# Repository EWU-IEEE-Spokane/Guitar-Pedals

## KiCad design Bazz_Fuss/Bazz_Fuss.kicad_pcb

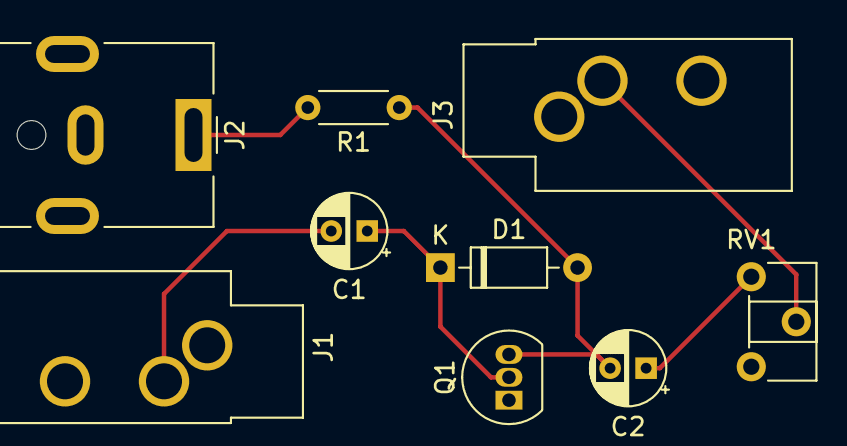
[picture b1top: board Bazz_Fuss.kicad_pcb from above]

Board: 2 copper layers, 9 parts (0 on the bottom side), 7 nets.

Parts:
C1, C2: C; CP_Radial_D4.0mm_P2.00mm
D1: 1N914; D_DO-35_SOD27_P7.62mm_Horizontal
J1, J3: AudioJack2; Jack_3.5mm_CUI_SJ1-3533NG_Horizontal_CircularHoles
J2: Barrel_Jack; BarrelJack_CUI_PJ-063AH_Horizontal
Q1: 2N3904; TO-92_Inline
R1: R; R_Axial_DIN0204_L3.6mm_D1.6mm_P5.08mm_Horizontal
RV1: R_POT; Potentiometer_ACP_CA6-H2,5_Horizontal

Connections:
GND: J1.S, J2.2, J3.S, Q1.1, RV1.3
unnamed: C1.1, D1.1, Q1.2
unnamed: C1.2, J1.T
unnamed: C2.1, RV1.1
unnamed: C2.2, D1.2, Q1.3, R1.1
unnamed: J2.1, R1.2
unnamed: J3.T, RV1.2

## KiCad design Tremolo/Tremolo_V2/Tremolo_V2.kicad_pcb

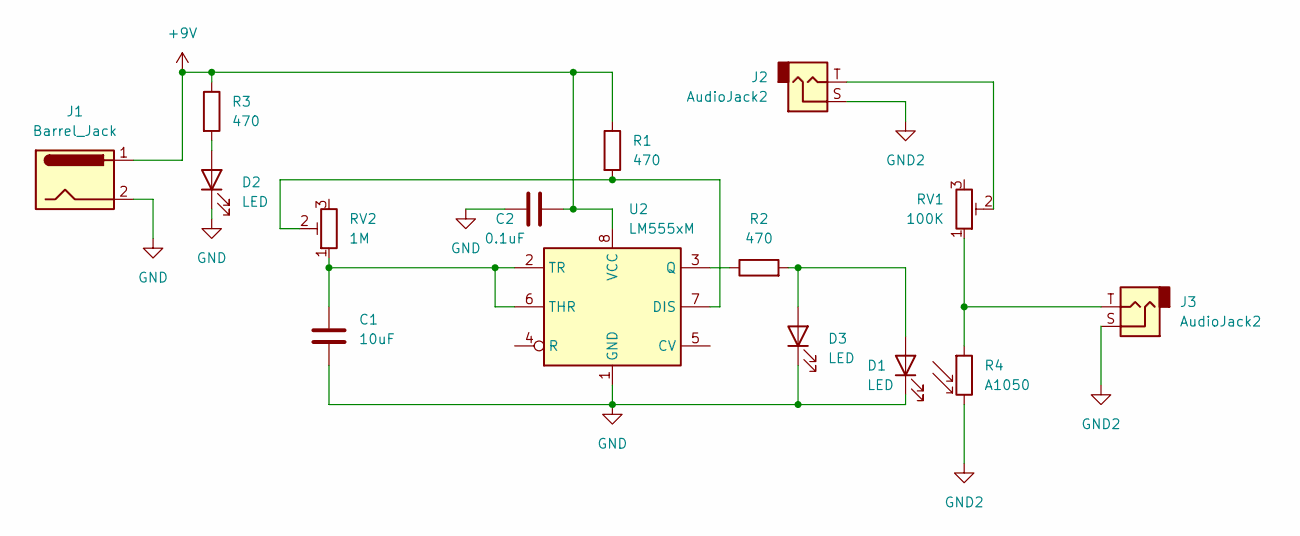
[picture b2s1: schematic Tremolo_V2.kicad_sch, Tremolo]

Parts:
C1: 10uF; C_Disc_D4.3mm_W1.9mm_P5.00mm
C2: 0.1uF; C_Disc_D3.0mm_W2.0mm_P2.50mm
D1, D2, D3: LED; LED_D3.0mm
J1: Barrel_Jack; BarrelJack_CUI_PJ-063AH_Horizontal
J2, J3: AudioJack2; CUI_MJ-63022B
R1, R2, R3: 470; R_Axial_DIN0207_L6.3mm_D2.5mm_P7.62mm_Horizontal
R4: A1050; R_LDR_D6.4mm_P3.4mm_Vertical
RV1: 100K; Potentiometer_Bourns_PTV09A-1_Single_Vertical
RV2: 1M; Bourns PDB12
U2: LM555xM; SOIC-8_3.9x4.9mm_P1.27mm

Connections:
+9V: C2.2, J1.1, R1.1, R3.1, U2.8 (VCC)
GND: C1.2, C2.1, D1.1 (K), D2.1 (K), D3.1 (K), J1.2, U2.1 (GND)
GND2: J2.S, J3.S, R4.2
unnamed: C1.1, RV2.1, U2.2 (TR), U2.6 (THR)
unnamed: D1.2 (A), D3.2 (A), R2.2
unnamed: D2.2 (A), R3.2
unnamed: J2.T, RV1.2
unnamed: J3.T, R4.1, RV1.1
unnamed: R1.2, RV2.2, U2.7 (DIS)
unnamed: R2.1, U2.3 (Q)

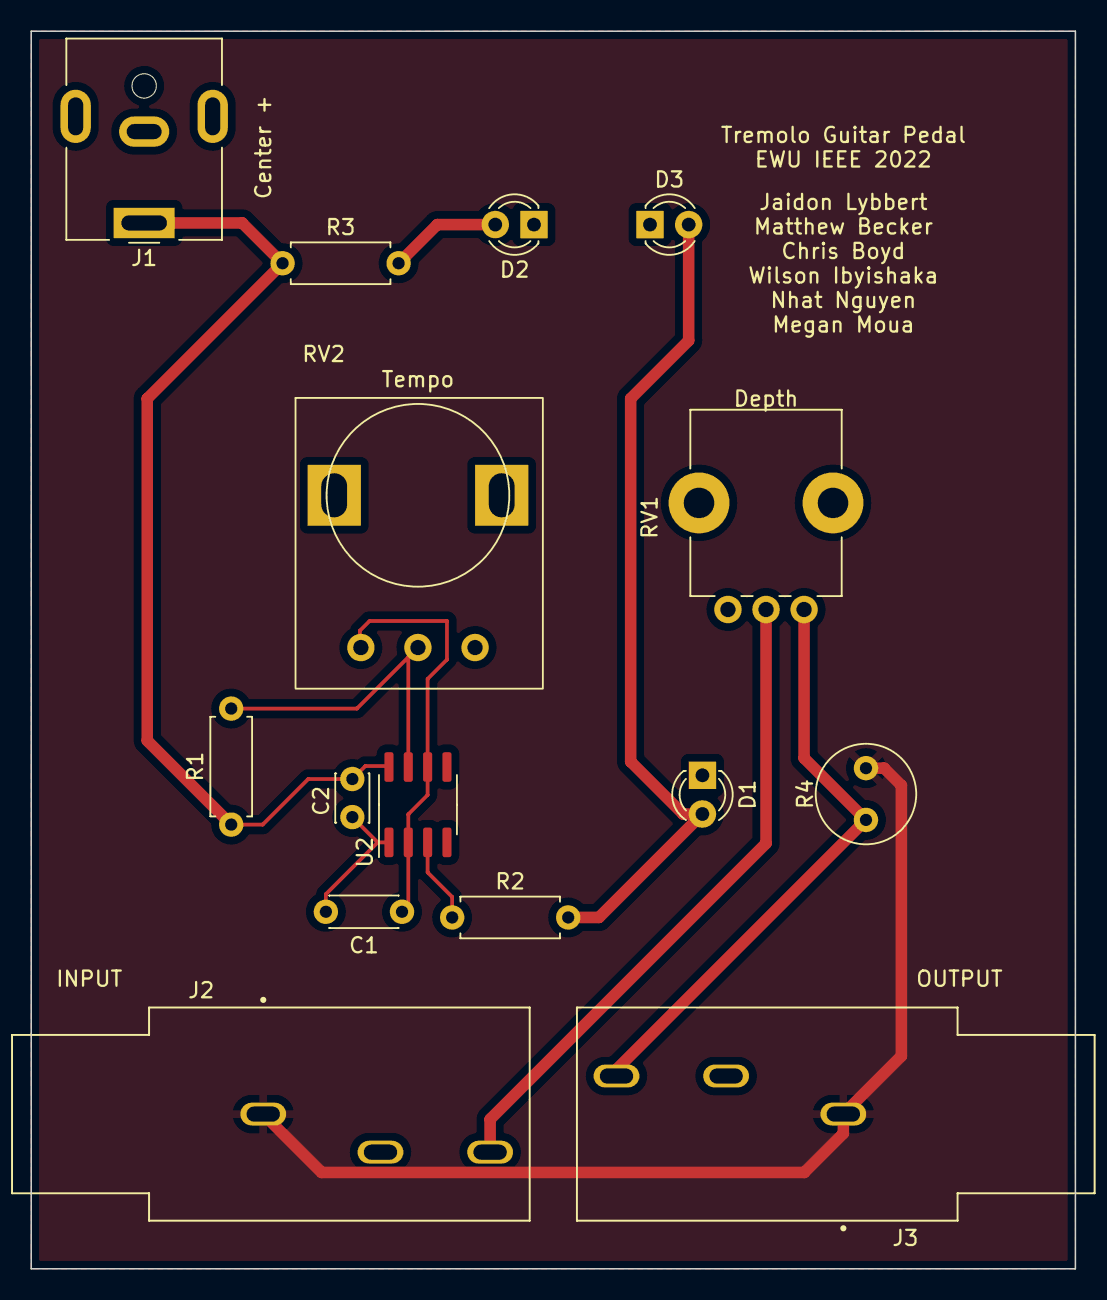
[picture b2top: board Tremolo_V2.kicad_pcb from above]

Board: 2 copper layers, 68.6 x 81.3 mm, 15 parts (0 on the bottom side), 10 nets.

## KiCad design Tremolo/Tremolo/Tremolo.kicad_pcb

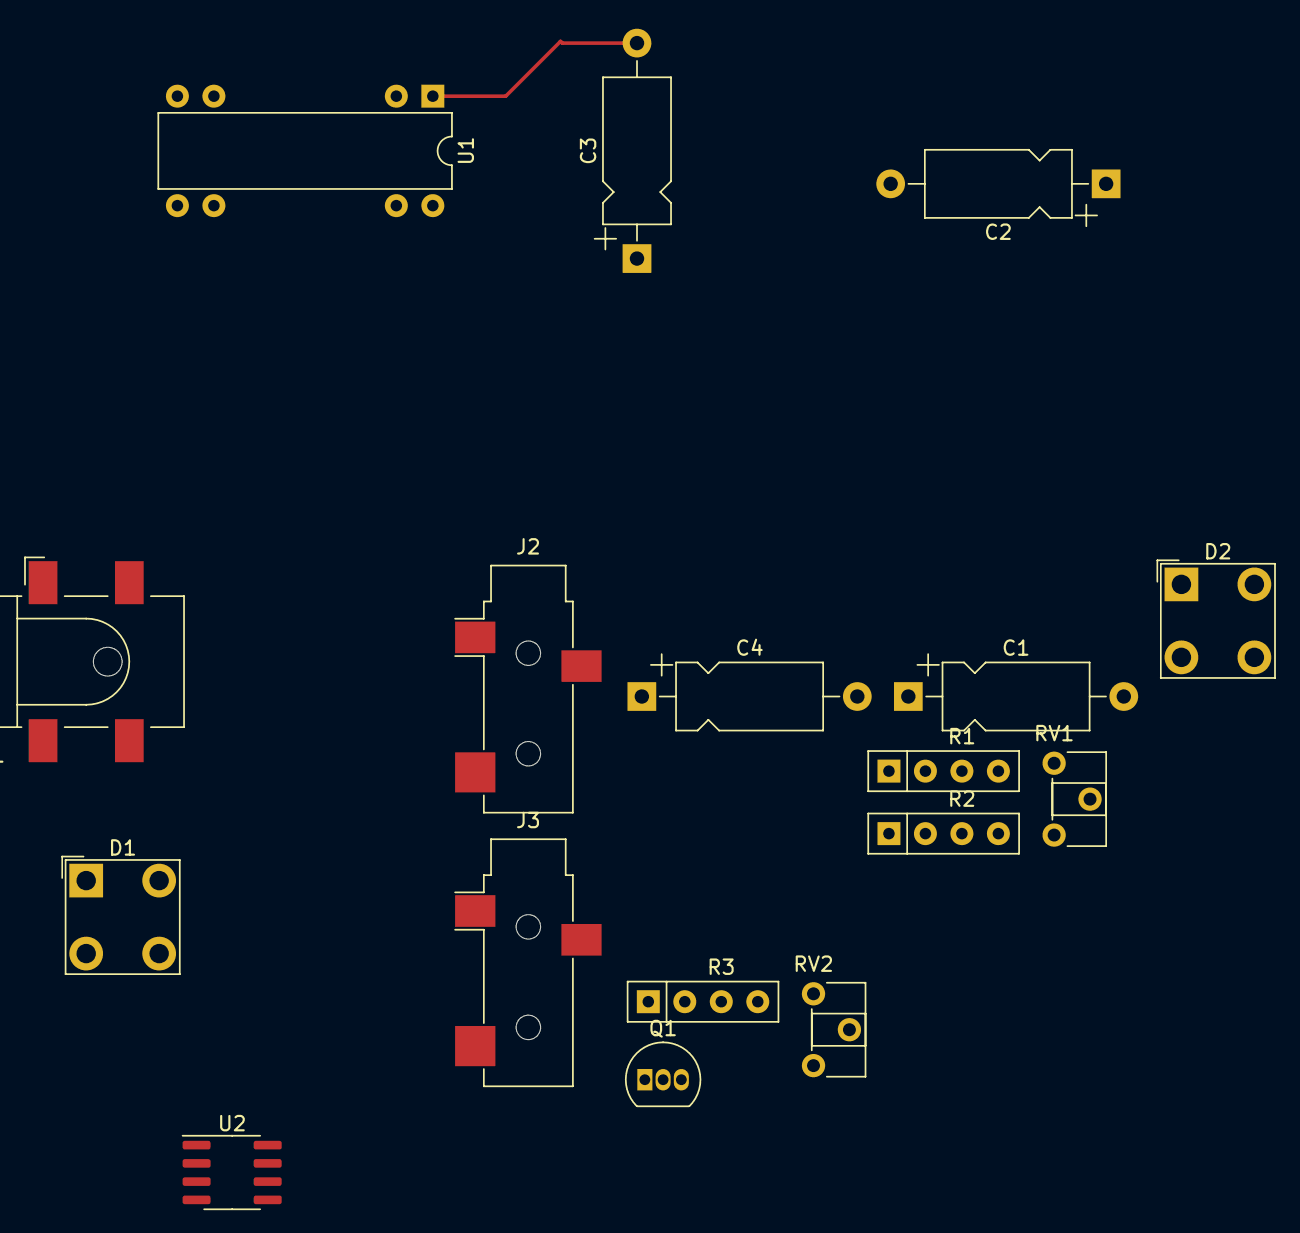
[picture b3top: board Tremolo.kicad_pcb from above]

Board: 2 copper layers, 17 parts (0 on the bottom side), 15 nets.

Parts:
C1, C3: 10uF; CP_Axial_L10.0mm_D4.5mm_P15.00mm_Horizontal
C2: 0.1uF; CP_Axial_L10.0mm_D4.5mm_P15.00mm_Horizontal
C4: 220uF; CP_Axial_L10.0mm_D4.5mm_P15.00mm_Horizontal
D1, D2: LED; LED_BL-FL7680RGB
J1: Barrel_Jack; BarrelJack_CLIFF_FC681465S_SMT_Horizontal
J2, J3: AudioJack2; Jack_3.5mm_CUI_SJ-3523-SMT_Horizontal
Q1: 2N3905; TO-92_Inline
R1, R2, R3: 470; R_Array_SIP4
RV1: 100K; Potentiometer_ACP_CA6-H2,5_Horizontal
RV2: 1M; Potentiometer_ACP_CA6-H2,5_Horizontal
U1: LM386; DIP-8-16_W7.62mm
U2: LM555xM; SOIC-8_3.9x4.9mm_P1.27mm

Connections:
GND: C1.2, D1.1 (K), D2.1 (K), J1.2, J2.S, J3.S, RV1.1, U1.2 (-), U1.4 (GND), U2.1 (GND)
unnamed: C1.1, RV2.1, U2.2 (TR), U2.6 (THR)
unnamed: C2.1, RV1.2
unnamed: C2.2, U1.3 (+)
unnamed: C3.1, U1.8 (GAIN)
unnamed: C3.2, U1.1 (GAIN)
unnamed: C4.1, J3.T
unnamed: C4.2, U1.5
unnamed: D1.2 (A), R2.1, U2.3 (Q)
unnamed: D2.2 (A), J1.1, R1.1, R3.1, U2.8 (VCC)
unnamed: J2.T, RV1.3
unnamed: Q1.1 (E), U1.6 (V+)
unnamed: Q1.2 (B), R2.2
unnamed: Q1.3 (C), R3.2
unnamed: R1.2, RV2.2, U2.7 (DIS)

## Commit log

2020-12-15 Added readthedocs folder
2021-05-27 Updated documentation
2021-12-21 Added specifications for Tremolo
2021-12-21 Added spice model
2022-01-18 Added Tremolo pedal
2022-02-13 Added KiCAD design files for bazz fuss
2022-02-13 Added soundbyte
2022-02-13 Added soundbyte mp3
2022-02-14 Added 3D CAD for Tremolo enclosure
2022-02-14 Added images to documentation, added Tremolo page
2022-02-14 Added Tremolo enclosure CAD image
2022-02-14 Added simulation results for Tremolo pedal
